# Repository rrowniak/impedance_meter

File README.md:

# Impedance Meter - a tool for measuring input and output impedance

## Details
More details coming soon, check out my [blog](http://rrowniak.com)

## Author

Rafal Rowniak

## License

GPL-3.0 for non commercial use cases

For commercial use cases please contact the author.

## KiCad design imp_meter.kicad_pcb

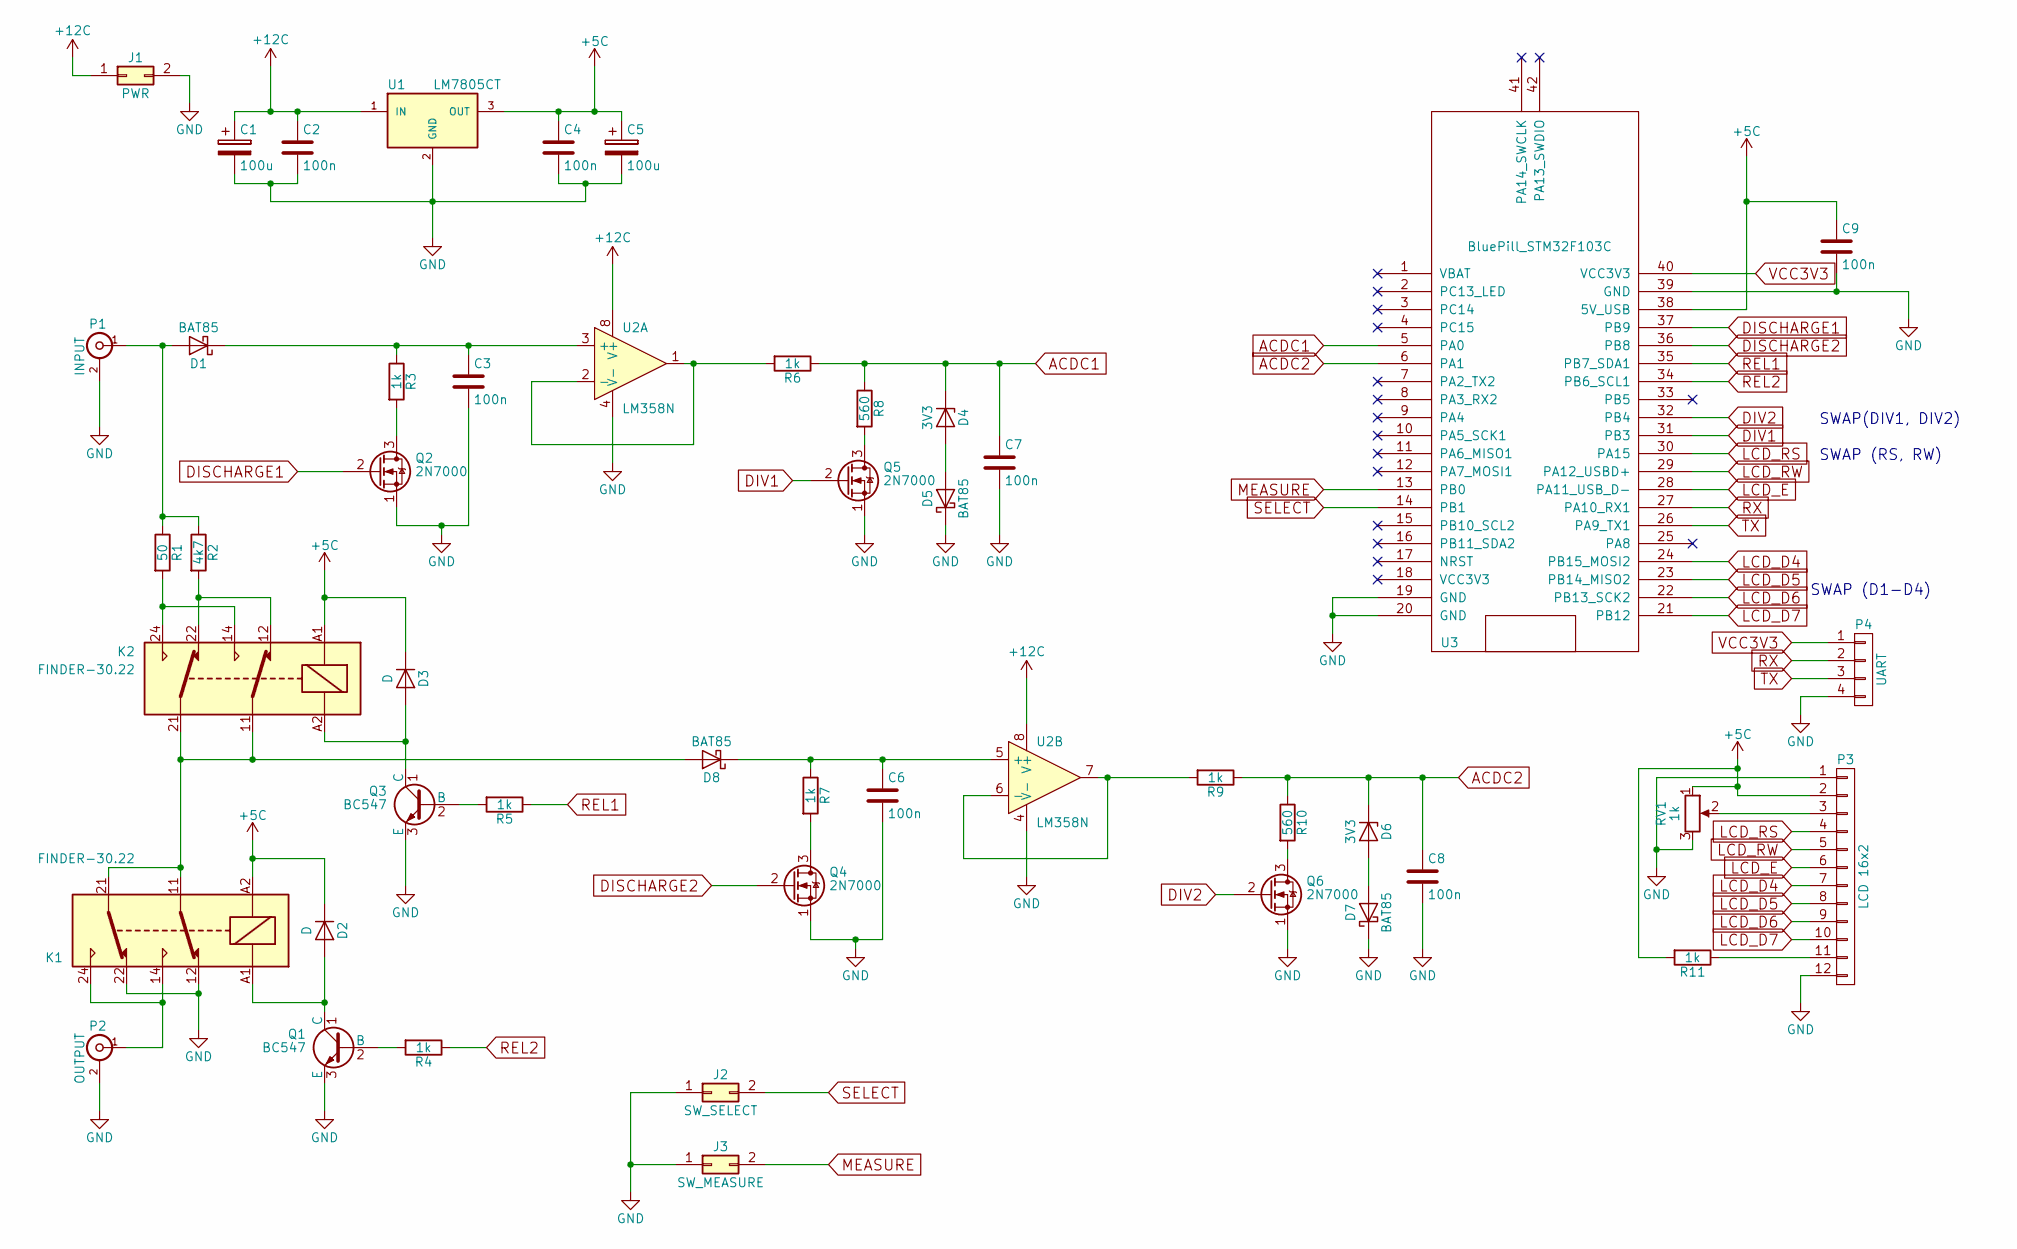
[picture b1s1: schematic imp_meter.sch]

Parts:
C1, C5: 100u; CP_Radial_D8.0mm_P5.00mm
C2, C3, C4, C6, C7, C8, C9: 100n; C_Disc_D3_P2.5
D1, D5, D7, D8: BAT85; D_A-405_P7.62mm_Horizontal
D2, D3: D; D_A-405_P7.62mm_Horizontal
D4, D6: 3V3; D_A-405_P7.62mm_Horizontal
J1: PWR; Pin_Header_Straight_2x01
J2: SW_SELECT; Pin_Header_Straight_2x01
J3: SW_MEASURE; Pin_Header_Straight_2x01
K1, K2: FINDER-30.22; Relay_DPDT_Finder_30.22
P1: INPUT; bnc-ci
P2: OUTPUT; bnc-ci
P3: LCD 16x2; Pin_Header_Straight_1x12
P4: UART; Pin_Header_Straight_1x04
Q1, Q3: BC547
Q2, Q4, Q5, Q6: 2N7000; TO-92_Molded_Narrow_Oval
R1: 50; R_Axial_DIN0411_L9.9mm_D3.6mm_P15.24mm_Horizontal
R2: 4k7; R_Axial_DIN0207_L6.3mm_D2.5mm_P10.16mm_Horizontal
R3, R4, R5, R6, R7, R9, R11: 1k; R_Axial_DIN0207_L6.3mm_D2.5mm_P10.16mm_Horizontal
R8, R10: 560; R_Axial_DIN0207_L6.3mm_D2.5mm_P10.16mm_Horizontal
RV1: 1k; Potentiometer_ACP_CA9-V10_Vertical
U1: LM7805CT; TO-220
U2: LM358N; DIP-8_W7.62mm_LongPads
U3: BluePill_STM32F103C

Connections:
+5C: C4.1, C5.1, C9.1, D2.1 (K), D3.1 (K), K1.A2, K2.A1, P3.2, R11.2, RV1.1, U1.3 (OUT), U3.38 (5V_USB)
+12C: C1.1, C2.1, J1.1, U1.1 (IN), U2.8 (V+)
ACDC1: C7.1, D4.1 (K), R6.1, R8.1, U3.5 (PA0)
ACDC2: C8.1, D6.1 (K), R9.1, R10.1, U3.6 (PA1)
DISCHARGE1: Q2.2 (G), U3.37 (PB9)
DISCHARGE2: Q4.2 (G), U3.36 (PB8)
DIV1: Q5.2 (G), U3.31 (PB3)
DIV2: Q6.2 (G), U3.32 (PB4)
GND: C1.2, C2.2, C3.2, C4.2, C5.2, C6.2, C7.2, C8.2, C9.2, D5.1 (K), D7.1 (K), J1.2, J2.1, J3.1, K1.12, K1.22, P1.2 (Ext), P2.2 (Ext), P3.1, P3.12, P4.4, Q1.3 (E), Q2.1 (S), Q3.3 (E), Q4.1 (S), Q5.1 (S), Q6.1 (S), RV1.3, U1.2 (GND), U2.4 (V-), U3.19 (GND), U3.20 (GND), U3.39 (GND)
LCD_D4: P3.7, U3.24 (PB15_MOSI2)
LCD_D5: P3.8, U3.23 (PB14_MISO2)
LCD_D6: P3.9, U3.22 (PB13_SCK2)
LCD_D7: P3.10, U3.21 (PB12)
LCD_E: P3.6, U3.28 (PA11_USB_D-)
LCD_RS: P3.4, U3.30 (PA15)
LCD_RW: P3.5, U3.29 (PA12_USBD+)
MEASURE: J3.2, U3.13 (PB0)
unnamed: C3.1, D1.1 (K), R3.1, U2.3 (+)
unnamed: D1.2 (A), P1.1 (In), R1.1, R2.1
unnamed: D2.2 (A), K1.A1, Q1.1 (C)
unnamed: D3.2 (A), K2.A2, Q3.1 (C)
unnamed: D4.2 (A), D5.2 (A)
unnamed: D6.2 (A), D7.2 (A)
unnamed: K1.14, K1.24, P2.1 (In)
unnamed: K2.12, K2.22, R2.2
unnamed: K2.14, K2.24, R1.2
unnamed: P3.3, RV1.2
unnamed: P3.11, R11.1
unnamed: Q1.2 (B), R4.2
unnamed: Q2.3 (D), R3.2
unnamed: Q3.2 (B), R5.2
unnamed: Q4.3 (D), R7.2
unnamed: Q5.3 (D), R8.2
unnamed: Q6.3 (D), R10.2
unnamed: R6.2, U2.1, U2.2 (-)
unnamed: R9.2, U2.6 (-), U2.7
REL1: R5.1, U3.35 (PB7_SDA1)
REL2: R4.1, U3.34 (PB6_SCL1)
RX: P4.2, U3.27 (PA10_RX1)
SELECT: J2.2, U3.14 (PB1)
TX: P4.3, U3.26 (PA9_TX1)
VCC3V3: P4.1, U3.40 (VCC3V3)

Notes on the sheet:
SWAP (RS, RW)
SWAP (D1-D4)
SWAP(DIV1, DIV2)

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
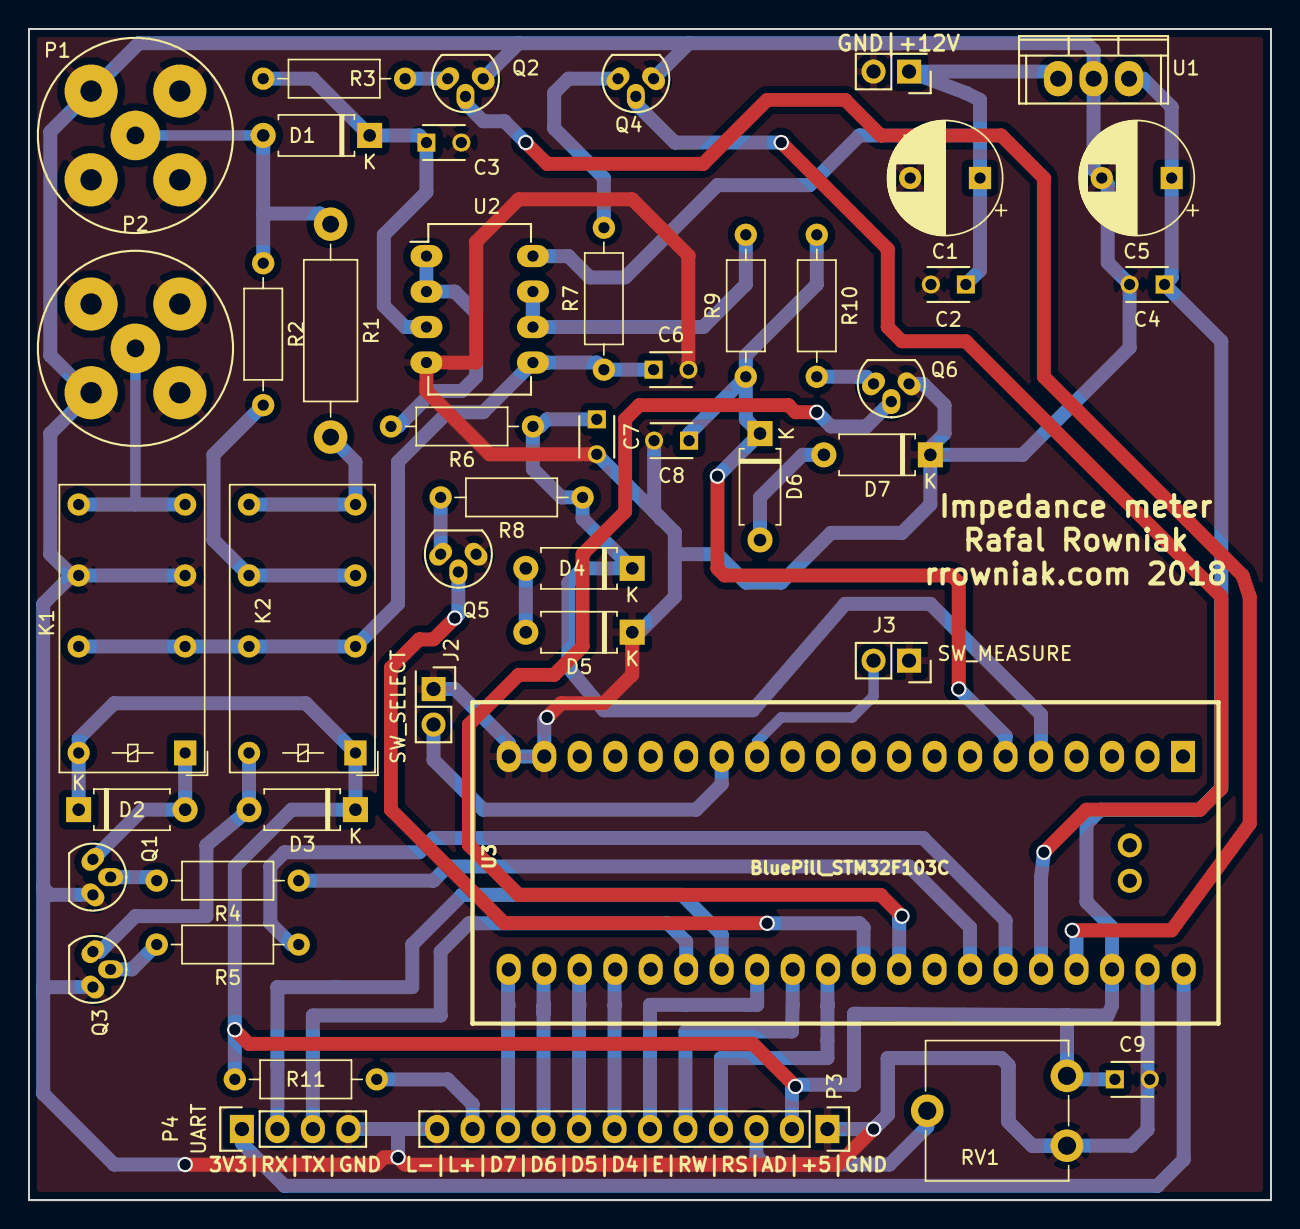
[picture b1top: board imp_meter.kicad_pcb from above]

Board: 2 copper layers, 88.9 x 83.8 mm, 46 parts (0 on the bottom side), 43 nets.

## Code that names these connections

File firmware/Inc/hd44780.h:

#ifndef __hd44780_h
#define __hd44780_h

#include "main.h"
#include <stdint.h>

#define LCD_CTRL_PORT LCD_PIN_E_GPIO_Port
#define LCD_RS LCD_PIN_RS_Pin
#define LCD_RW LCD_PIN_RW_Pin
#define LCD_EN LCD_PIN_E_Pin

#define LCD_DATA_PORT LCD_PIN_D4_GPIO_Port
#define LCD_D4 LCD_PIN_D4_Pin
#define LCD_D5 LCD_PIN_D5_Pin
#define LCD_D6 LCD_PIN_D6_Pin
#define LCD_D7 LCD_PIN_D7_Pin

#define LCD_COL_COUNT 16
#define LCD_ROW_COUNT 2

void lcd_init(void);

void lcd_command(uint8_t command);
void lcd_write(uint8_t value);

void lcd_on(void);
void lcd_off(void);

void lcd_clear(void);
void lcd_return_home(void);

void lcd_enable_blinking(void);
void lcd_disable_blinking(void);

void lcd_enable_cursor(void);
void lcd_disable_cursor(void);

void lcd_scroll_left(void);
void lcd_scroll_right(void);

void lcd_set_left_to_right(void);
void lcd_set_right_to_left(void);

void lcd_enable_autoscroll(void);
void lcd_disable_autoscroll(void);

void lcd_create_char(uint8_t location, uint8_t *charmap);

void lcd_set_cursor(uint8_t col, uint8_t row);

void lcd_puts(char *string);
void lcd_println(char *string, uint8_t line);
void lcd_printf(char *format, ...);
void lcd_printfln(char *format, ...);

#endif // __hd44780_h

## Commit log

2018-06-24 Firmware added
2018-06-24 Improved measurements
2018-06-24 Fixed shunt resistor value
2018-06-27 Some bugs related to measurements fixed
2018-07-01 Fixed several bugs related to Input imp measurement
2018-07-06 Modified README.md
2018-07-06 Small improvements to README.md
2018-07-12 Added error correction based on linear interpolation
2018-07-12 Typo fixed
2018-07-14 Small structure refactoring
2018-12-02 Added PCB project
